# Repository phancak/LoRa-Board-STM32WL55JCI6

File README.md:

# LoRa-Board-STM32WL55JCI6
 Desc

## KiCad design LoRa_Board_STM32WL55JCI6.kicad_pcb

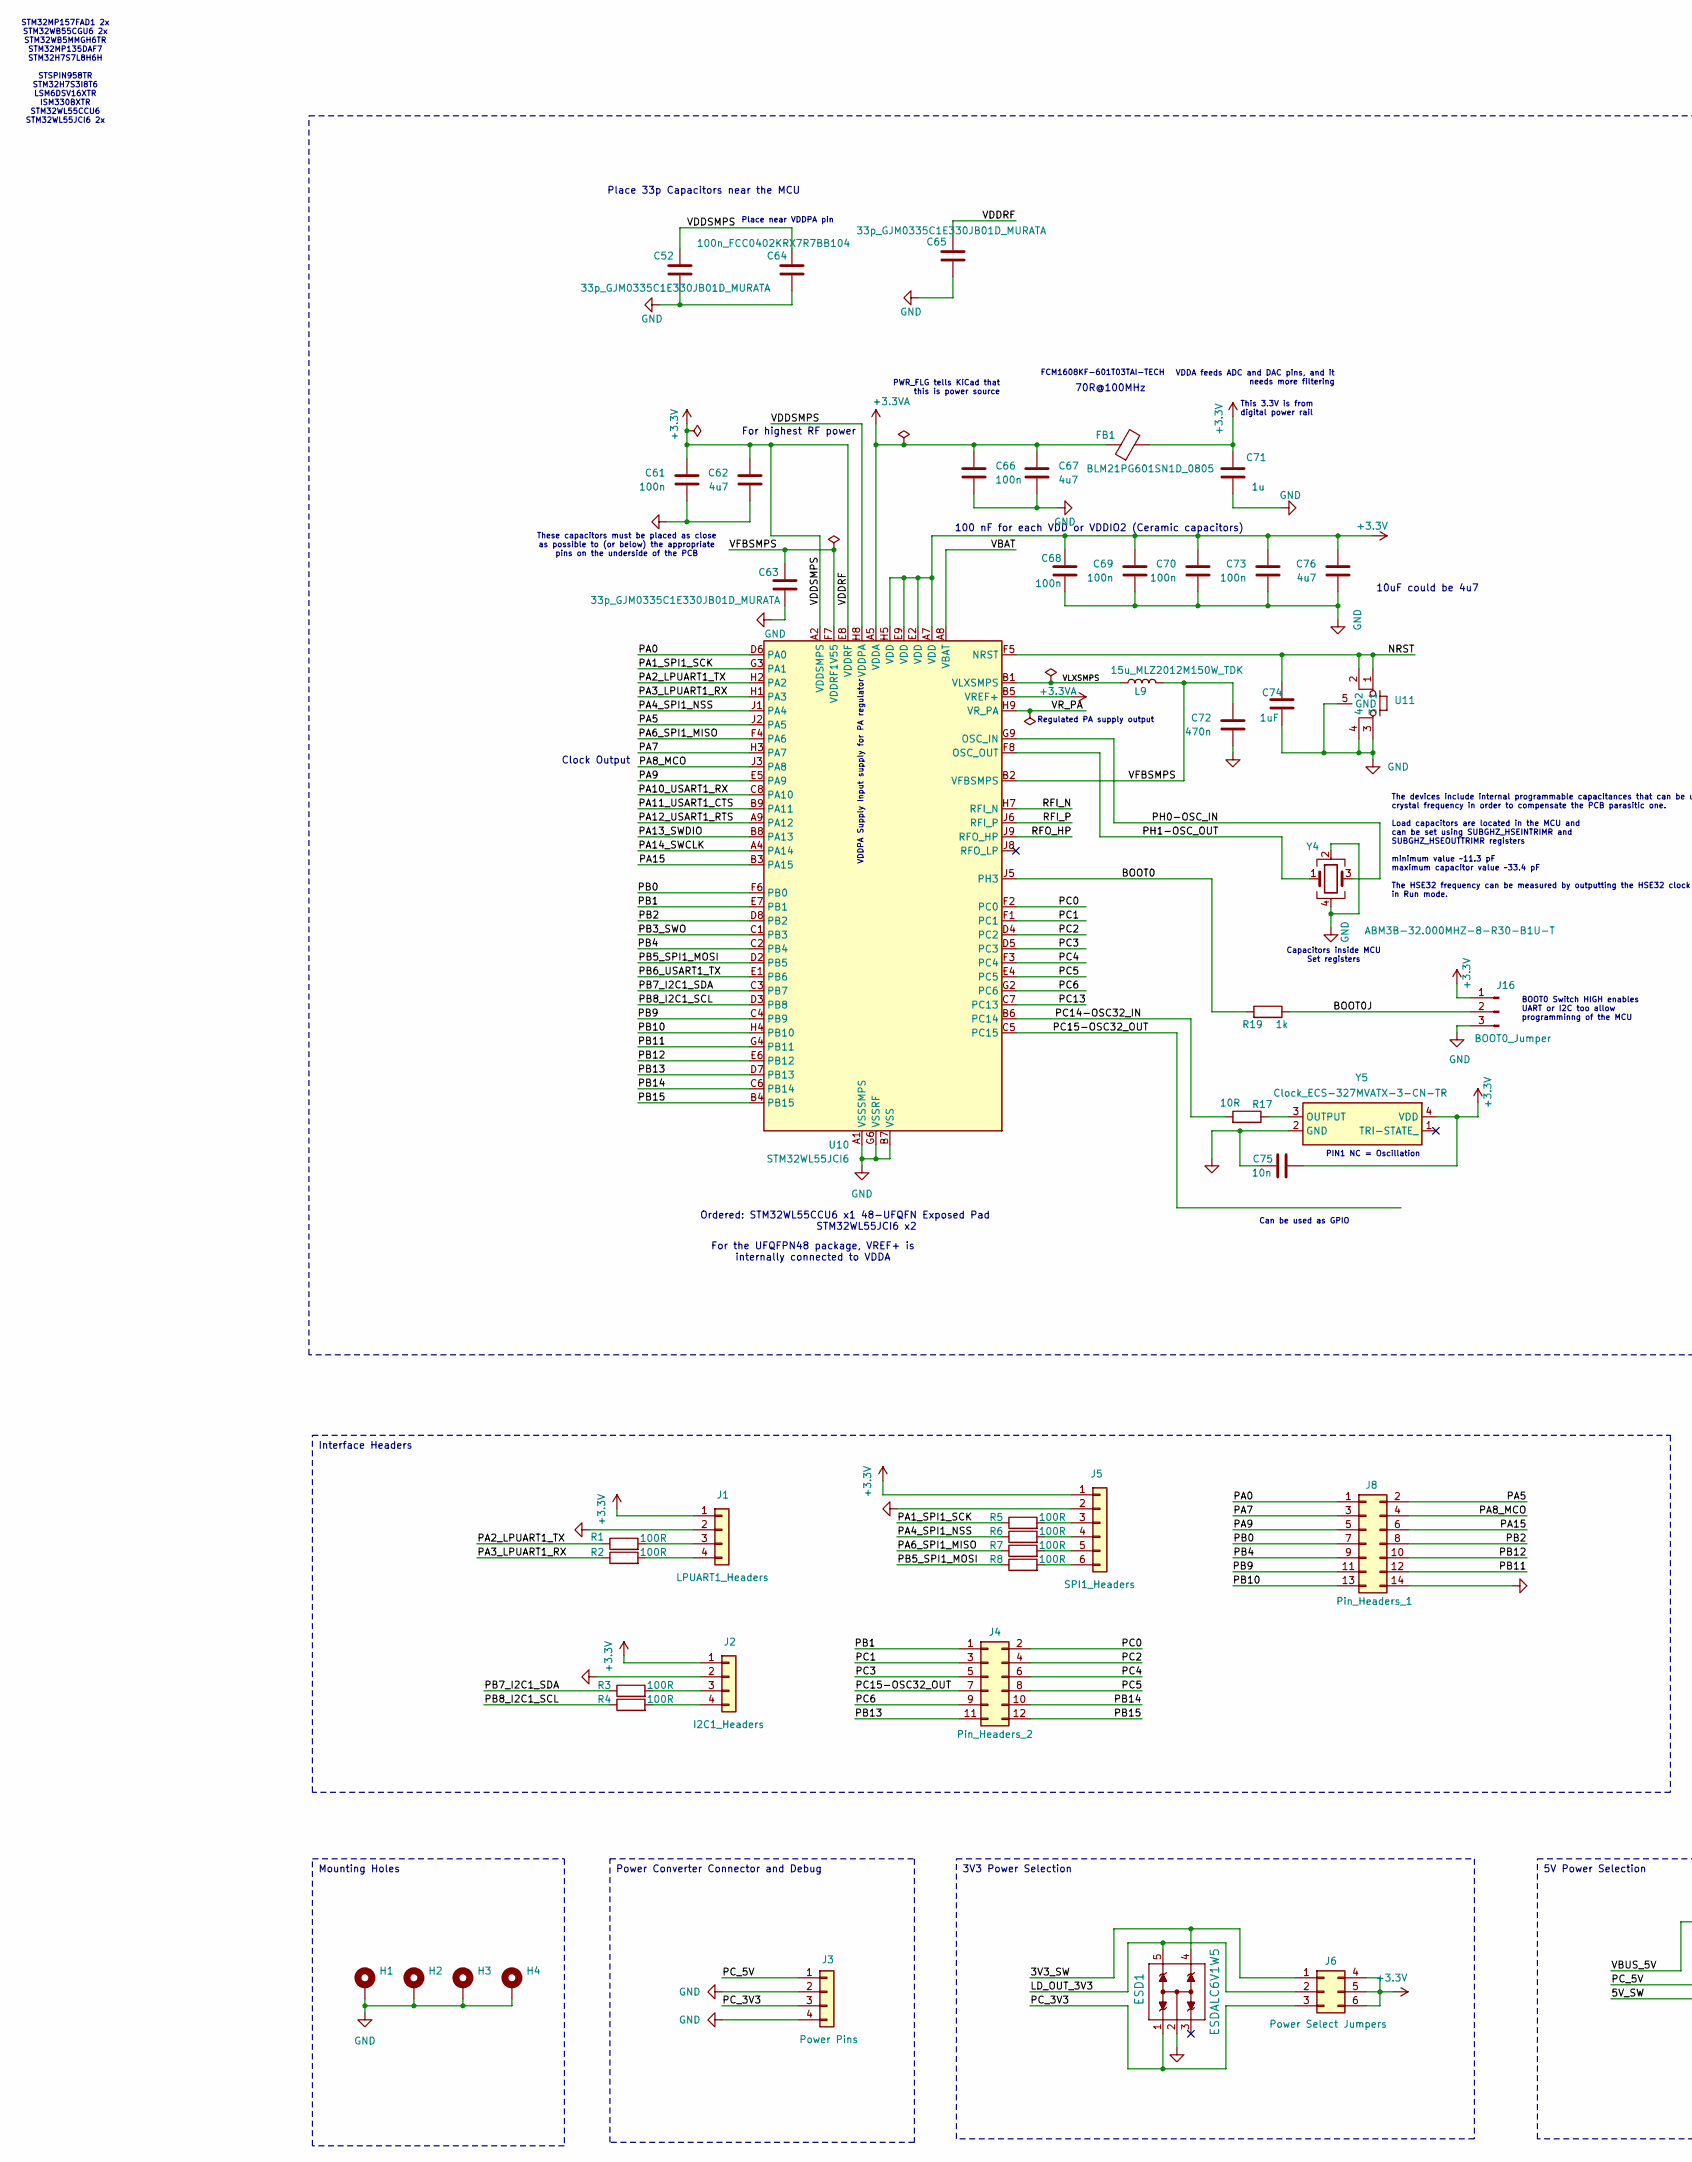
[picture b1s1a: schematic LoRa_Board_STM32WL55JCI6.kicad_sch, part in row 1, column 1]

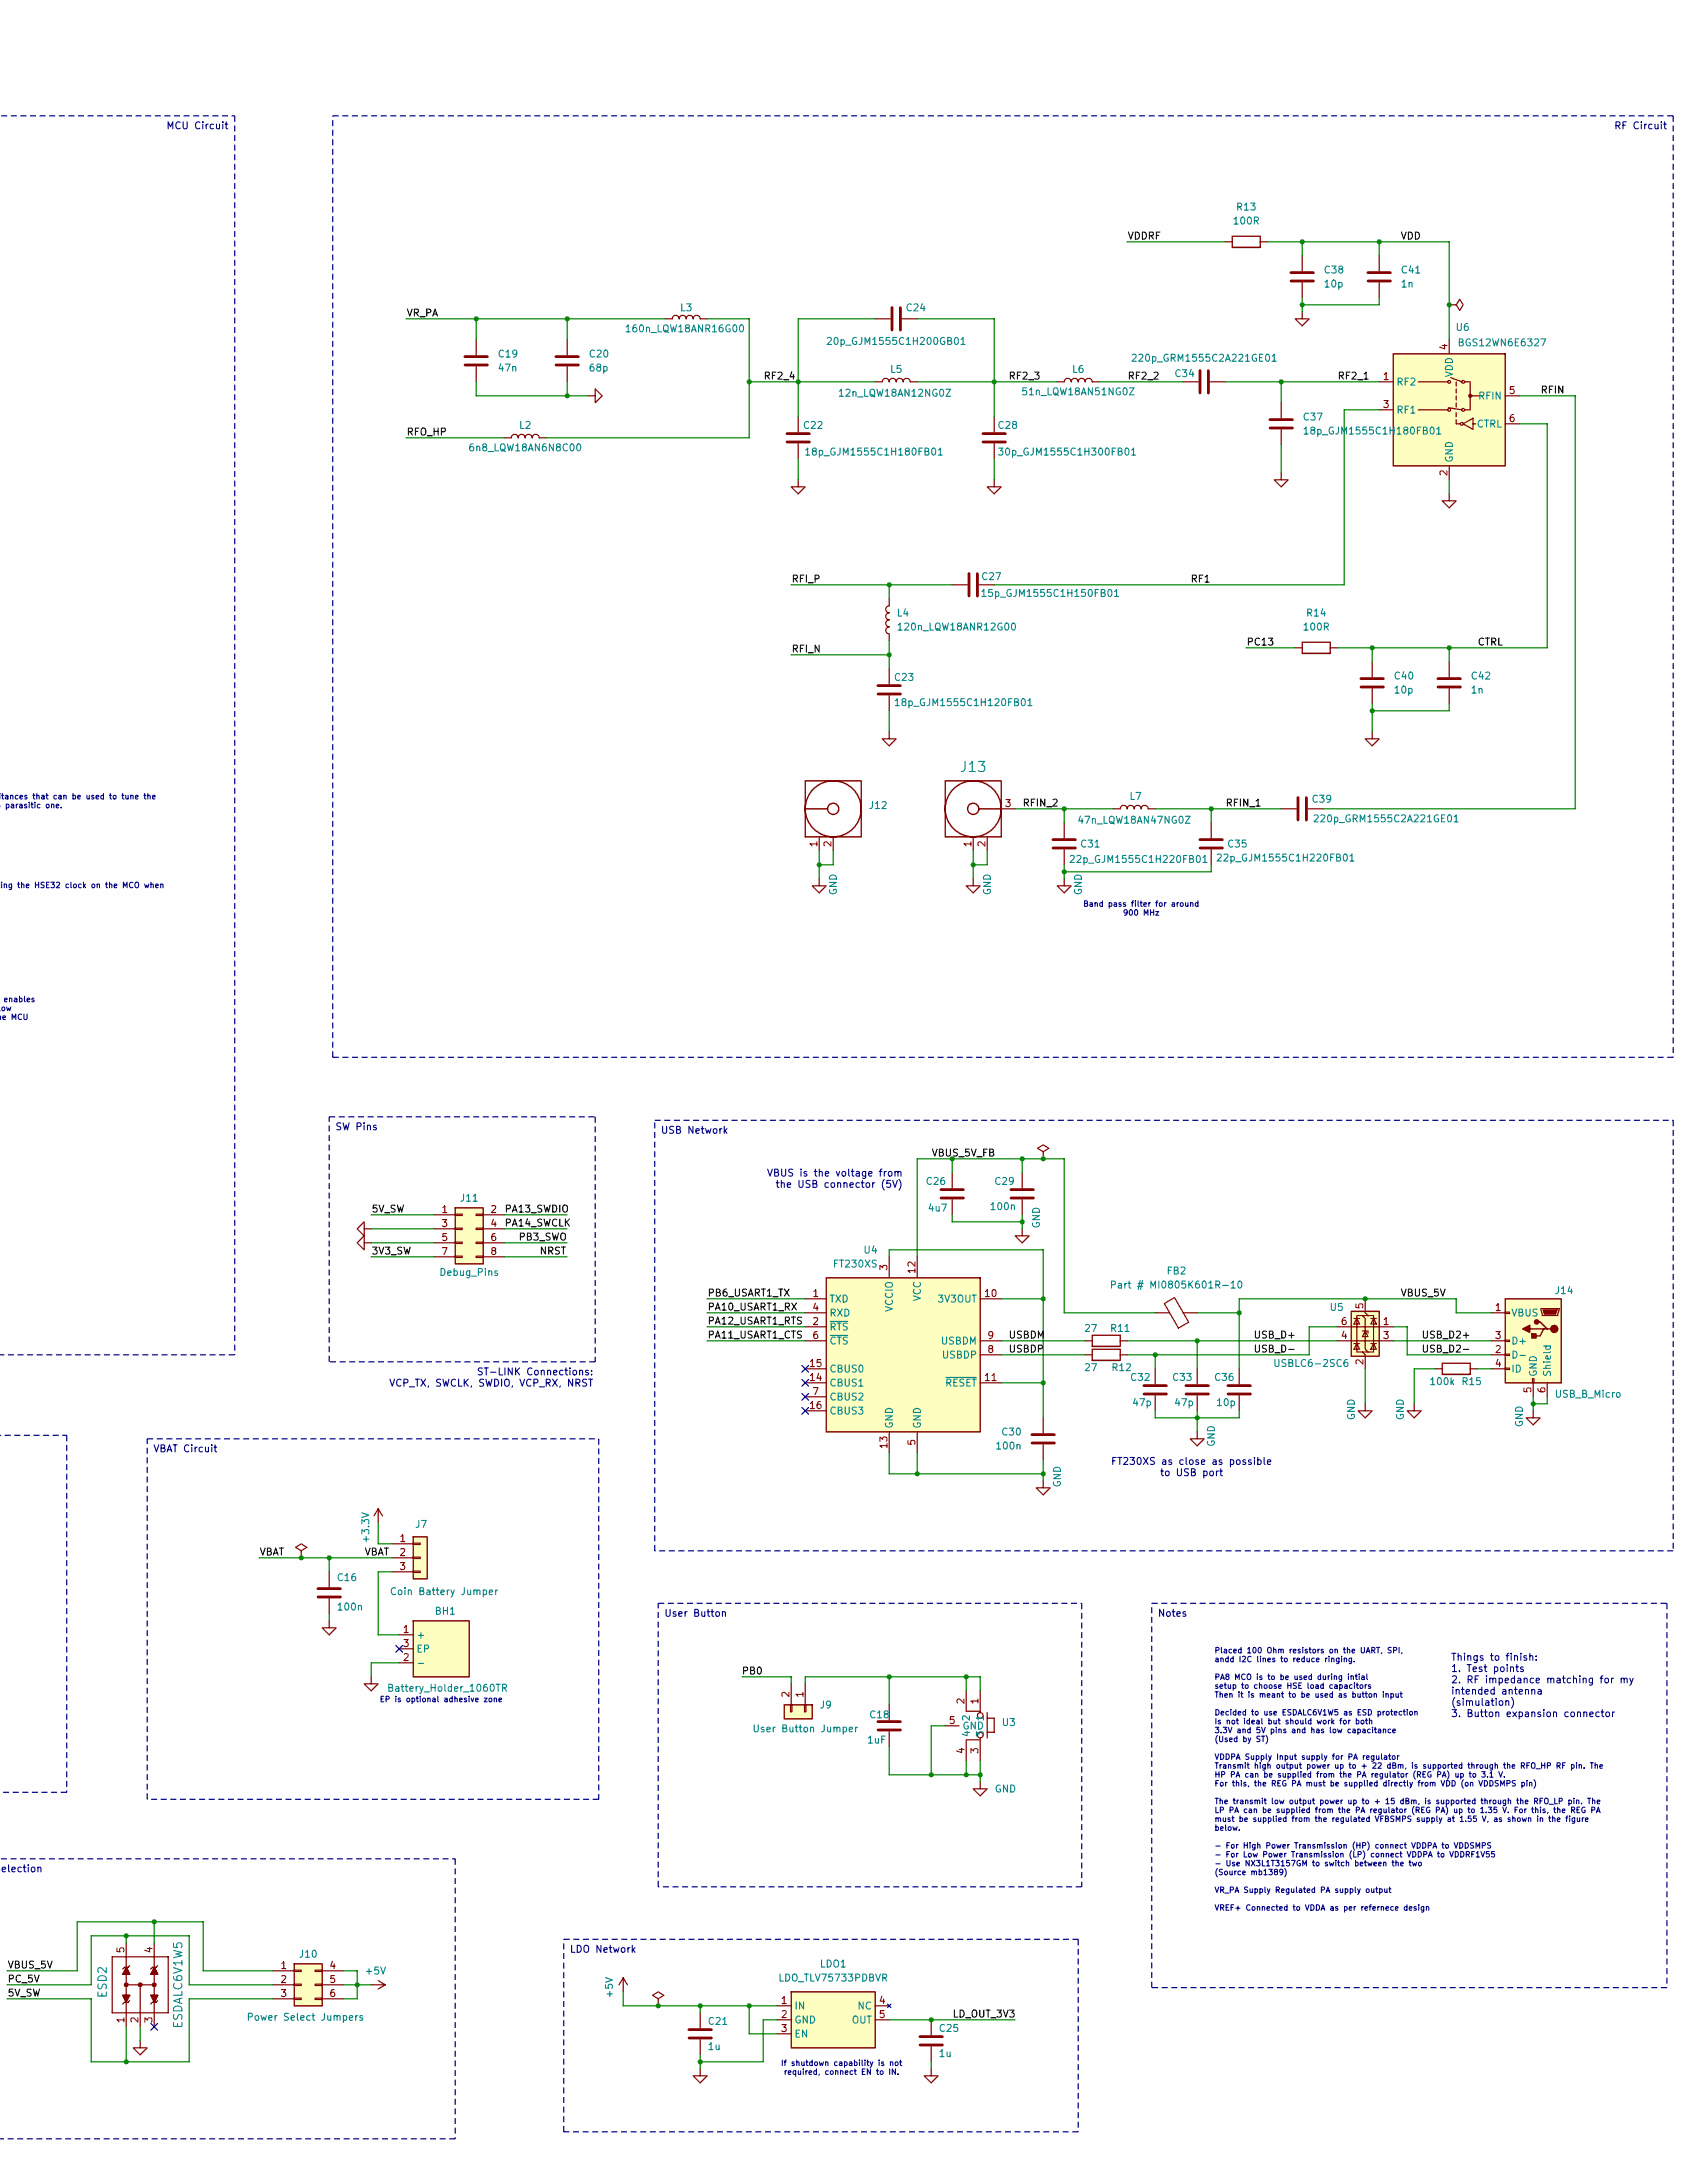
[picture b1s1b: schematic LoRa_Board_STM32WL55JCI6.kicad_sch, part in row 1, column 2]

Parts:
BH1: Battery_Holder_1060TR; Mouser Part Number 534-1060TR
C16, C29, C30, C61, C66, C68, C69, C70, C73: 100n; C_0805_2012Metric_Pad1.18x1.45mm_HandSolder
C18, C74: 1uF; C_0805_2012Metric_Pad1.18x1.45mm_HandSolder
C19: 47n; C_0805_2012Metric_Pad1.18x1.45mm_HandSolder
C20: 68p; C_0805_2012Metric_Pad1.18x1.45mm_HandSolder
C21, C25, C71: 1u; C_0805_2012Metric_Pad1.18x1.45mm_HandSolder
C22, C37: 18p_GJM1555C1H180FB01; C_0805_2012Metric_Pad1.18x1.45mm_HandSolder
C23: 18p_GJM1555C1H120FB01; C_0805_2012Metric_Pad1.18x1.45mm_HandSolder
C24: 20p_GJM1555C1H200GB01; C_0805_2012Metric_Pad1.18x1.45mm_HandSolder
C26, C62, C67, C76: 4u7; C_0805_2012Metric_Pad1.18x1.45mm_HandSolder
C27: 15p_GJM1555C1H150FB01; C_0805_2012Metric_Pad1.18x1.45mm_HandSolder
C28: 30p_GJM1555C1H300FB01; C_0805_2012Metric_Pad1.18x1.45mm_HandSolder
C31, C35: 22p_GJM1555C1H220FB01; C_0805_2012Metric_Pad1.18x1.45mm_HandSolder
C32, C33: 47p; C_0805_2012Metric_Pad1.18x1.45mm_HandSolder
C34, C39: 220p_GRM1555C2A221GE01; C_0805_2012Metric_Pad1.18x1.45mm_HandSolder
C36, C38, C40: 10p; C_0805_2012Metric_Pad1.18x1.45mm_HandSolder
C41, C42: 1n; C_0805_2012Metric_Pad1.18x1.45mm_HandSolder
C52, C63, C65: 33p_GJM0335C1E330JB01D_MURATA; C_0805_2012Metric_Pad1.18x1.45mm_HandSolder
C64: 100n_FCC0402KRX7R7BB104; C_0805_2012Metric_Pad1.18x1.45mm_HandSolder
C72: 470n; C_0805_2012Metric_Pad1.18x1.45mm_HandSolder
C75: 10n; C_0805_2012Metric_Pad1.18x1.45mm_HandSolder
ESD1, ESD2: ESDALC6V1W5; SOT323-5L_STM-L
FB1: BLM21PG601SN1D_0805; C_0805_2012Metric_Pad1.18x1.45mm_HandSolder
FB2: Part # MI0805K601R-10; C_0805_2012Metric_Pad1.18x1.45mm_HandSolder
H1, H2, H3, H4: MountingHole_Pad; MountingHole_3.2mm_M3_Pad
J1: LPUART1_Headers; PinHeader_1x04_P2.54mm_Vertical
J2: I2C1_Headers; PinHeader_1x04_P2.54mm_Vertical
J3: Power Pins; PinHeader_1x04_P2.54mm_Vertical
J4: Pin_Headers_2; PinHeader_2x06_P2.54mm_Vertical
J5: SPI1_Headers; PinHeader_1x06_P2.54mm_Vertical
J6, J10: Power Select Jumpers; PinHeader_2x03_P2.54mm_Vertical_PINS
J7: Coin Battery Jumper; PinHeader_1x03_P2.54mm_Vertical
J8: Pin_Headers_1; PinHeader_2x07_P2.54mm_Vertical
J9: User Button Jumper; PinHeader_1x02_P2.54mm_Vertical
J11: Debug_Pins; PinHeader_2x04_P2.54mm_Vertical
J12: SMA Clip Mount Adapter (bottom)
J13: SMA PCB END LAUNCH JACK ROUND PO; SMA Clip Mount Adapter (top); Manufacturer Part Number 60311002111526
J14: USB_B_Micro; USB_Micro-B_Molex-105017-0001
J16: BOOT0_Jumper; PinHeader_1x03_P2.54mm_Vertical
L2: 6n8_LQW18AN6N8C00; L_0603_1608Metric_Pad1.05x0.95mm_HandSolder
L3: 160n_LQW18ANR16G00; L_0603_1608Metric_Pad1.05x0.95mm_HandSolder
L4: 120n_LQW18ANR12G00; L_0603_1608Metric_Pad1.05x0.95mm_HandSolder
L5: 12n_LQW18AN12NG0Z; L_0603_1608Metric_Pad1.05x0.95mm_HandSolder
L6: 51n_LQW18AN51NG0Z; L_0603_1608Metric_Pad1.05x0.95mm_HandSolder
L7: 47n_LQW18AN47NG0Z; L_0603_1608Metric_Pad1.05x0.95mm_HandSolder
L9: 15u_MLZ2012M150W_TDK; L_0805_2012Metric_Pad1.15x1.40mm_HandSolder
LDO1: LDO_TLV75733PDBVR; LDO_SOT95P280X145-5N; Mouser Part Number 595-TLV75733PDBVR
R1, R2, R3, R4, R5, R6, R7, R8, R13, R14: 100R; R_0805_2012Metric_Pad1.20x1.40mm_HandSolder
R11, R12: 27; R_0805_2012Metric_Pad1.20x1.40mm_HandSolder
R15: 100k; R_0805_2012Metric_Pad1.20x1.40mm_HandSolder
R17: 10R; R_0805_2012Metric_Pad1.20x1.40mm_HandSolder
R19: 1k; R_0805_2012Metric_Pad1.20x1.40mm_HandSolder
U3, U11: Button_KMR231GLFS
U4: FT230XS; SSOP-16_3.9x4.9mm_P0.635mm
U5: USBLC6-2SC6; SOT-23-6
U6: BGS12WN6E6327; Infineon_PG-TSNP-6-10_0.7x1.1mm_0.7x1.1mm_P0.4mm
U10: STM32WL55JCI6; ST_UFBGA-73_5x5mm_Layout9x9_P0.5mm
Y4: ABM3B-32.000MHZ-8-R30-B1U-T; XTAL_ABM3B-32.000MHZ-10-R30-B1U-T
Y5: Clock_ECS-327MVATX-3-CN-TR; Clock_ECS327MVATX7CNTR; Mouser Part Number 520-327MVATX-7-CNT

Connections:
+3.3V: C52.1, C61.1, C62.1, C64.1, C65.1, C68.1, C69.1, C70.1, C71.1, C73.1, C75.2, C76.1, FB1.2, J1.1, J2.1, J5.1, J6.4, J6.5, J6.6, J7.1, J16.1, R13.1, U10.A2 (VDDSMPS), U10.A7 (VDD), U10.E2 (VDD), U10.E8 (VDDRF), U10.E9 (VDD), U10.H5 (VDD), U10.H8 (VDDPA), Y5.4 (VDD)
+3.3VA: C66.1, C67.1, FB1.1, U10.A5 (VDDA), U10.B5 (VREF+)
+5V: C21.1, J10.4, J10.5, J10.6, LDO1.1 (IN), LDO1.3 (EN)
/3V3_SW: ESD1.4 (I/O3), J6.1, J11.7
/5V_SW: ESD2.1 (I/O1), J10.3, J11.1
/BOOT0: R19.2, U10.J5 (PH3)
/BOOT0J: J16.2, R19.1
/CTRL: C40.2, C42.2, R14.2, U6.6 (CTRL)
/LD_OUT_3V3: C25.1, ESD1.5 (I/O4), J6.2, LDO1.5 (OUT)
/NRST: C74.2, J11.8, U10.F5 (NRST), U11.1, U11.2
/PA0: J8.1, U10.D6 (PA0)
/PA1_SPI1_SCK: R5.1, U10.G3 (PA1)
/PA2_LPUART1_TX: R1.1, U10.H2 (PA2)
/PA3_LPUART1_RX: R2.1, U10.H1 (PA3)
/PA4_SPI1_NSS: R6.1, U10.J1 (PA4)
/PA5: J8.2, U10.J2 (PA5)
/PA6_SPI1_MISO: R7.1, U10.F4 (PA6)
/PA7: J8.3, U10.H3 (PA7)
/PA8_MCO: J8.4, U10.J3 (PA8)
/PA9: J8.5, U10.E5 (PA9)
/PA10_USART1_RX: U4.4 (RXD), U10.C8 (PA10)
/PA11_USART1_CTS: U4.6 (~CTS), U10.B9 (PA11)
/PA12_USART1_RTS: U4.2 (~RTS), U10.A9 (PA12)
/PA13_SWDIO: J11.2, U10.B8 (PA13)
/PA14_SWCLK: J11.4, U10.A4 (PA14)
/PA15: J8.6, U10.B3 (PA15)
/PB0: J8.7, J9.2, U10.F6 (PB0)
/PB1: J4.1, U10.E7 (PB1)
/PB2: J8.8, U10.D8 (PB2)
/PB3_SWO: J11.6, U10.C1 (PB3)
/PB4: J8.9, U10.C2 (PB4)
/PB5_SPI1_MOSI: R8.1, U10.D2 (PB5)
/PB6_USART1_TX: U4.1 (TXD), U10.E1 (PB6)
/PB7_I2C1_SDA: R3.1, U10.C3 (PB7)
/PB8_I2C1_SCL: R4.1, U10.D3 (PB8)
/PB9: J8.11, U10.C4 (PB9)
/PB10: J8.13, U10.H4 (PB10)
/PB11: J8.12, U10.G4 (PB11)
/PB12: J8.10, U10.E6 (PB12)
/PB13: J4.11, U10.D7 (PB13)
/PB14: J4.10, U10.C6 (PB14)
/PB15: J4.12, U10.B4 (PB15)
/PC0: J4.2, U10.F2 (PC0)
/PC1: J4.3, U10.F1 (PC1)
/PC2: J4.4, U10.D4 (PC2)
/PC3: J4.5, U10.D5 (PC3)
/PC4: J4.6, U10.F3 (PC4)
/PC5: J4.8, U10.E4 (PC5)
/PC6: J4.9, U10.G2 (PC6)
/PC13: R14.1, U10.C7 (PC13)
/PC14-OSC32_IN: R17.2, U10.B6 (PC14)
/PC15-OSC32_OUT: J4.7, U10.C5 (PC15)
/PC_3V3: ESD1.1 (I/O1), J3.3, J6.3
/PC_5V: ESD2.5 (I/O4), J3.1, J10.2
/PH0-OSC_IN: U10.G9 (OSC_IN), Y4.3
/PH1-OSC_OUT: U10.F8 (OSC_OUT), Y4.1
/RF1: C27.2, U6.3 (RF1)
/RF2_1: C34.2, C37.2, U6.1 (RF2)
/RF2_2: C34.1, L6.2
/RF2_3: C24.2, C28.2, L5.2, L6.1
/RF2_4: C22.2, C24.1, L2.2, L3.2, L5.1
/RFIN: C39.2, U6.5 (RFIN)
/RFIN_1: C35.2, C39.1, L7.2
/RFIN_2: C31.2, J13.3 (Signal), L7.1
/RFI_N: C23.2, L4.1, U10.H7 (RFI_N)
/RFI_P: C27.1, L4.2, U10.J6 (RFI_P)
/RFO_HP: L2.1, U10.J9 (RFO_HP)
/USBDM: R11.2, U4.9 (USBDM)
/USBDP: R12.2, U4.8 (USBDP)
/USB_D2+: J14.3 (D+), U5.3 (I/O2)
/USB_D2-: J14.2 (D-), U5.1 (I/O1)
/USB_D+: C33.1, R11.1, U5.4 (I/O2)
/USB_D-: C32.1, R12.1, U5.6 (I/O1)
/VBAT: C16.1, J7.2, U10.A8 (VBAT)
/VBUS_5V: C36.1, ESD2.4 (I/O3), FB2.1, J10.1, J14.1 (VBUS), U5.5 (VBUS)
/VBUS_5V_FB: C26.1, C29.1, FB2.2, U4.12 (VCC)
/VDD: C38.2, C41.2, R13.2, U6.4 (VDD)
/VFBSMPS: C63.1, C72.1, L9.1, U10.B2 (VFBSMPS), U10.F7 (VDDRF1V55)
/VLXSMPS: L9.2, U10.B1 (VLXSMPS)
/VR_PA: C19.1, C20.1, L3.1, U10.H9 (VR_PA)
GND: BH1.2 (-), C16.2, C18.1, C19.2, C20.2, C21.2, C22.1, C23.1, C25.2, C26.2, C28.1, C29.2, C30.2, C31.1, C32.2, C33.2, C35.1, C36.2, C37.1, C38.1, C40.1, C41.1, C42.1, C52.2, C61.2, C62.2, C63.2, C64.2, C65.2, C66.2, C67.2, C68.2, C69.2, C70.2, C71.2, C72.2, C73.2, C74.1, C75.1, C76.2, ESD1.2 (GND), ESD2.2 (GND), H1.1, H2.1, H3.1, H4.1, J1.2, J2.2, J3.2, J3.4, J5.2, J8.14, J11.3, J11.5, J12.1 (GND), J12.2 (GND), J13.1 (GND), J13.2 (GND), J14.5 (GND), J14.6 (Shield), J16.3, LDO1.2 (GND), R15.1, U3.3, U3.4, U3.5 (GND), U4.5 (GND), U4.13 (GND), U5.2 (GND), U6.2 (GND), U10.A1 (VSSSMPS), U10.B7 (VSS), U10.D9 (VSS), U10.E3 (VSS), U10.G5 (VSS), U10.G6 (VSSRF), U10.G7 (VSSRF), U10.G8 (VSSRF), U10.H6 (VSSRF), U11.3, U11.4, U11.5 (GND), Y4.2, Y4.4, Y5.2 (GND)
unnamed: BH1.1 (+), J7.3
unnamed: J1.3, R1.2
unnamed: J1.4, R2.2
unnamed: J2.3, R3.2
unnamed: J2.4, R4.2
unnamed: J5.3, R5.2
unnamed: J5.4, R6.2
unnamed: J5.5, R7.2
unnamed: J5.6, R8.2
unnamed: C18.2, J9.1, U3.1, U3.2
unnamed: J14.4 (ID), R15.2
unnamed: C30.1, U4.3 (VCCIO), U4.10 (3V3OUT), U4.11 (~RESET)
unnamed: R17.1, Y5.3 (OUTPUT)

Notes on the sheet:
Notes
Mounting Holes
USB Network
5V Power Selection
Interface Headers
User Button
RF Circuit
Power Converter Connector and Debug
LDO Network
3V3 Power Selection
MCU Circuit
SW Pins
VBAT Circuit
PIN1 NC = Oscillation
FCM1608KF-601T03TAI-TECH
The devices include internal programmable capacitances that can be used to tune the crystal frequency in order to compensate the PCB parasitic one. Load capacitors are located in the MCU and can be set using SUBGHZ_HSEINTRIMR and SUBGHZ_HSEOUTTRIMR registers minimum value ~11.3 pF maximum capacitor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
EP is optional adhesive zone
Place near VDDPA pin
70R@100MHz
If shutdown capability is not required, connect EN to IN.
Place 33p Capacitors near the MCU
Ordered: STM32WL55CCU6 x1 48-UFQFN Exposed Pad STM32WL55JCI6 x2
Regulated PA supply output
Capacitors inside MCU Set registers
Placed 100 Ohm resistors on the UART, SPI, andd I2C lines to reduce ringing. PA8 MCO is to be used during intial setup to choose HSE load capacitors Then it is meant to be used as button input Decided to use ESDALC6V1W5 as ESD protection Is not ideal but should work for both 3.3V and 5V pins and ha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
VDDPA Supply Input supply for PA regulator
Band pass filter for around 900 MHz
PWR_FLG tells KiCad that this is power source
ST-LINK Connections: VCP_TX, SWCLK, SWDIO, VCP_RX, NRST
STM32MP157FAD1 2x STM32WB55CGU6 2x STM32WB5MMGH6TR STM32MP135DAF7 STM32H7S7L8H6H STSPIN958TR STM32H7S3I8T6 LSM6DSV16XTR ISM330BXTR STM32WL55CCU6 STM32WL55JCI6 2x
For the UFQFPN48 package, VREF+ is internally connected to VDDA
These capacitors must be placed as close as possible to (or below) the appropriate pins on the underside of the PCB
BOOT0 Switch HIGH enables UART or I2C too allow programminng of the MCU
10uF could be 4u7
Clock Output
Things to finish: 1. Test points 2. RF impedance matching for my intended antenna (simulation) 3. Button expansion connector
For highest RF power
VDDA feeds ADC and DAC pins, and it needs more filtering
100 nF for each VDD or VDDIO2 (Ceramic capacitors)
VBUS is the voltage from the USB connector (5V)

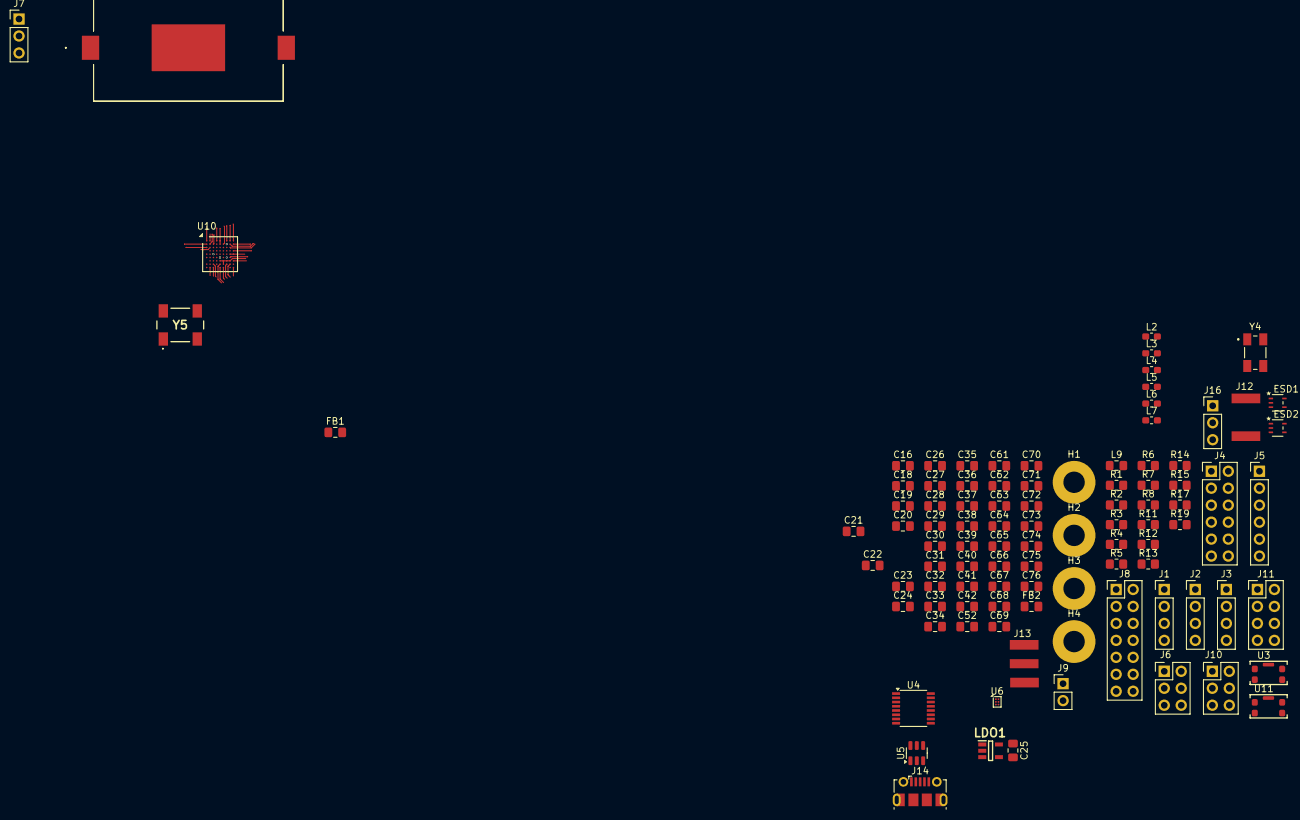
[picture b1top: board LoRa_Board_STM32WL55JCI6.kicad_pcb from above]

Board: 4 copper layers, 98 parts (0 on the bottom side), 94 nets.
